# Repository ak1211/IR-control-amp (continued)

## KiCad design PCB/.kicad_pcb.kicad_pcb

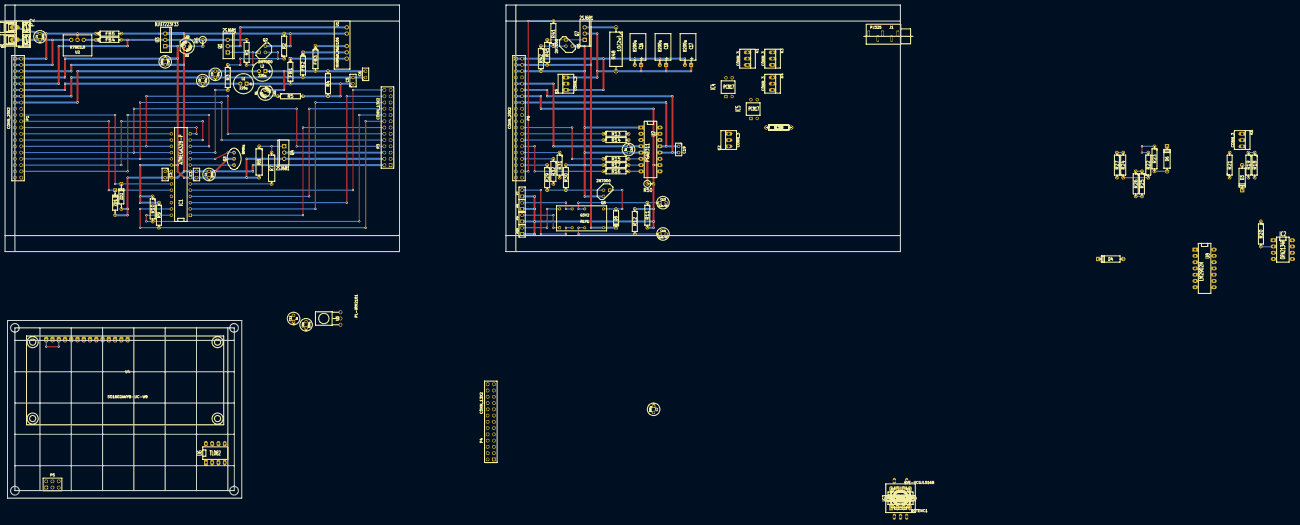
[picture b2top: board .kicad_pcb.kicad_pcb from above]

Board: 2 copper layers, 363.2 x 200.0 mm, 125 parts (0 on the bottom side), 102 nets.

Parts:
C1, C7, C10, C11: 100u; C1V5
C2, C3, C5, C6, C19: 0.1u; C1
C4: 220u; C1V5
C8, C9: 47u; C1V5
C12, C15: 1u; C1V5
C13, C14: 2.2u BP; C1V5
C16, C17, C18: 8200u; C1V7H
D1, D2: LED; LED-5MM
D3, D4, D6, D7: DIODE; D4
D5: DIODE; D3
FB1, FB2, FB3, FB4, FB5: FILTER; CP4
IC1: ATMEGA328-P; DIP-28__300
IC2, IC3: OPA2134P; DIP-8__300_ELL
IC4, IC5: PC817; DIP-4__300
J1: PJ325
K1, K2, K3, K4, K5, K6: CONN_3; PINHEAD1-3
L1, L2: 220u; C1V8
P1, P6: CONN_20X2; PIN_ARRAY_20X2
P2: CONN_2; AK300-2
P3, P4: CONN_13X2; pin_array_13x2
P5: CONN_6; pin_array_3x2
P7, P8, P9, P10: CONN_2; PIN_ARRAY_2X1
Q1, Q4, Q7: 2SJ681; TO220_VERTGDS
Q2, Q5, Q6: 2N7000; TO92DGS
Q3: 8MHz; CERALOCK
R1, R2, R30, R38, R39, R42: 10k; R4
R3, R29, R41: 10; R4
R4, R13, R14, R15, R16: 1k; R4
R5, R9, R10, R23, R24, R27, R28: 4.7k; R4
R6: 4.7k; R1
R7: 10; R5
R8: 10k; R5
R11, R12, R17: 47k; R4
R18, R19, R20, R21, R22, R25, R26, R33, R40, R43, R44, R46, R47, R49: 100k; R4
R31, R32: 220; R4
R34, R35, R36, R37: 47; R4
R45: 33k; R4
R48: 10(2w); R7
R50: 0; R1
RLY1: G5V2; G5V-2
ROTENC1: EVE-VCGJL016B; EVEV
SW1: RESET_SW; SW_PUSH_SMALL
U1: MINMAX_MAU106; MAU106
U2: R78E5.0; RECOM_R78E
U3: NJU7223F33; TO220_VERT123
U4: SO1602AWYB-UC-WB; SO1602
U5: PL-IRM2161
U6: TL082; DIP-8__300_ELL
U7: PGA2311; DIP-16__300_ELL
U8: LM2902N; DIP-14__300_ELL
ZD1, ZD2: 3.3V; DO-41

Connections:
+3.3V: C1.1, C3.1, C10.1, C12.1, IC1.7, IC1.20, P1.7, P1.8, P3.4, P4.4, P5.2, P6.7, P6.8, Q4.S, R8.2, R9.1, R10.1, U3.1, U5.3
+5.0V: C8.1, C19.2, IC2.8, IC3.8, L1.2, P1.11, P1.12, P6.11, P6.12, U6.8, U7.12, U8.4
+5V: C7.1, C15.1, FB4.2, P1.9, P1.10, P6.9, P6.10, Q1.S, R1.2, R6.1, U3.2, U7.4
+12V: C4.1, D5.2, P1.3, P1.4, P2.2, P6.3, P6.4, Q7.S, R45.2, R48.1, RLY1.1, U2.1
-5.0V: C9.2, C19.1, IC2.4, IC3.4, L2.2, P1.15, P1.16, P6.15, P6.16, U6.4, U7.13, U8.11
/analog_board/1ch.L: P7.2, RLY1.6
/analog_board/1ch.R: P8.2, RLY1.11
/analog_board/2ch.L: P9.2, RLY1.8
/analog_board/2ch.R: P10.2, RLY1.9
/analog_board/EVOL_SCLK: P6.24, R15.1
/analog_board/EVOL_SDI: P6.28, R14.1
/analog_board/EVOL_~CS: P6.26, R13.1
/analog_board/INPUT_CH.L: P6.20, R33.2, U8.7
/analog_board/INPUT_CH.R: P6.22, R49.2, U8.14
/analog_board/INRASH_CURRENT_LIMITTER_GATE: P6.38, R41.2
/analog_board/LINE_OUT.L: J1.4, K4.3
/analog_board/LINE_OUT.R: J1.2, K3.3
/analog_board/MISO/MAIN_AMP_STANDBY: P6.32, R31.1
/analog_board/MOSI/EVOL_MUTE: P6.30, R16.1
/analog_board/SCK/MAIN_AMP_MUTE: P6.34, R32.1
/analog_board/SELECT_SOURCE_GATE: P6.36, R29.1
/mpu_board/ANALOG_PWR_GATE: IC1.11, R3.2
/mpu_board/EVOL_SCLK: IC1.14, P1.24
/mpu_board/EVOL_SDI: IC1.16, P1.28
/mpu_board/EVOL_~CS: IC1.15, P1.26
/mpu_board/I2C_SCL: IC1.28, P3.18, P4.18, R10.2, U4.7
/mpu_board/I2C_SDA: IC1.27, P3.16, P4.16, R9.2, U4.8, U4.9
/mpu_board/INPUT_CH.L: IC1.23, P1.20, ZD2.2
/mpu_board/INPUT_CH.R: IC1.24, P1.22, ZD1.2
/mpu_board/INPUT_SW: IC1.4, P3.20, P4.20, ROTENC1.S
/mpu_board/INRASH_CURRENT_LIMITTER_GATE: IC1.12, P1.38
/mpu_board/IR_RECEIVER: IC1.5, P3.26, P4.26, U5.1
/mpu_board/MISO/MAIN_AMP_STANDBY: IC1.18, P1.32, P3.8, P4.8, P5.1
/mpu_board/MOSI/EVOL_MUTE: IC1.17, P1.30, P3.12, P4.12, P5.4
/mpu_board/ROTARYENC_A: IC1.2, P3.22, P4.22, ROTENC1.A
/mpu_board/ROTARYENC_B: IC1.3, P3.24, P4.24, ROTENC1.B
/mpu_board/SCK/MAIN_AMP_MUTE: IC1.19, P1.34, P3.10, P4.10, P5.3
/mpu_board/SELECT_SOURCE_GATE: IC1.13, P1.36
/mpu_board/~DISPLAY_PWR_GATE: IC1.6, R7.2
/mpu_board/~RESET: IC1.1, P3.14, P4.14, P5.5, SW1.1
AGND: C5.2, C6.1, C8.2, C9.1, FB2.2, J1.1, K3.1, K4.1, P1.13, P1.14, P6.13, P6.14, P7.1, P8.1, P9.1, P10.1, R11.2, R12.1, R21.2, R22.2, R23.1, R24.1, R50.2, U7.10, U7.15, U8.3, U8.5, U8.10, U8.12
DGND: C1.2, C2.2, C3.2, C7.2, C10.2, C11.2, C12.2, C15.2, D2.2, FB5.2, IC1.8, IC1.22, IC4.2, IC5.2, P1.5, P1.6, P3.2, P4.2, P5.6, P6.5, P6.6, Q2.S, Q3.2, Q5.S, Q6.S, R2.2, R17.2, R30.2, R42.2, R50.1, ROTENC1.COM, SW1.2, U1.2, U3.3, U4.1, U4.3, U4.4, U5.2, U7.1, U7.5, ZD1.1, ZD2.1
GNDPWR: C4.2, C16.2, C17.2, C18.2, FB5.1, K5.1, P1.1, P1.2, P2.1, P6.1, P6.2, U2.2
LINE_IN_L: C14.2, U6.3, U7.16
LINE_IN_R: C13.2, U6.5, U7.9
unnamed: D1.1, R5.1
unnamed: P3.6, Q4.D
unnamed: FB4.1, U2.3
unnamed: Q4.G, R7.1, R8.1
unnamed: FB1.1, U1.6
unnamed: FB2.1, U1.5
unnamed: FB3.1, U1.4
unnamed: Q1.G, Q2.D, R1.1
unnamed: D2.1, R6.2
unnamed: C2.1, IC1.21
unnamed: C11.1, P4.6, U4.2
unnamed: Q1.D, U1.1
unnamed: IC1.10, Q3.3
unnamed: IC1.9, Q3.1
unnamed: C5.1, FB1.2, L1.1, R4.1, R5.2
unnamed: C6.2, D1.2, FB3.2, L2.1, R4.2
unnamed: Q2.G, R2.1, R3.1
unnamed: D6.2, R40.2, R43.1, U8.9
unnamed: R20.2, R25.2, R26.2, R33.1, U8.6
unnamed: IC4.1, R31.2
unnamed: D3.1, D4.2, U8.1
unnamed: R18.1, R20.1, U6.1, U6.2
unnamed: D3.2, R18.2, R19.1, U8.2
unnamed: D6.1, D7.2, U8.8
unnamed: R44.2, R46.2, R47.2, R49.1, U8.13
unnamed: C13.1, R11.1, RLY1.13
unnamed: C14.1, R12.2, RLY1.4
unnamed: R16.2, U7.8
unnamed: R15.2, U7.6
unnamed: R14.2, U7.3
unnamed: R13.2, U7.2
unnamed: Q6.D, Q7.G, R45.1
unnamed: R40.1, R44.1, U6.6, U6.7
unnamed: D5.1, Q5.D, RLY1.16
unnamed: R17.1, U7.7
unnamed: IC5.4, K2.1
unnamed: IC4.4, K1.1
unnamed: K1.3, R38.2
unnamed: K2.3, R39.2
unnamed: IC4.3, K1.2, R38.1
unnamed: IC5.3, K2.2, R39.1
unnamed: IC5.1, R32.2
unnamed: Q5.G, R29.2, R30.1
unnamed: D7.1, R43.2, R46.1, R47.1
unnamed: D4.1, R19.2, R25.1, R26.1
unnamed: IC2.7, IC3.5, R35.1
unnamed: IC2.5, R22.1, U7.14
unnamed: IC3.1, IC3.2, R36.1
unnamed: IC3.6, IC3.7, R37.1
unnamed: C16.1, C17.1, C18.1, K5.3, Q7.D, R48.2
unnamed: IC2.3, R21.1, U7.11
unnamed: J1.5, R28.2, R35.2, R37.2
unnamed: IC2.6, R24.2, R28.1
unnamed: IC2.1, IC3.3, R34.1
unnamed: J1.3, R27.2, R34.2, R36.2
unnamed: IC2.2, R23.2, R27.1
unnamed: Q6.G, R41.1, R42.1

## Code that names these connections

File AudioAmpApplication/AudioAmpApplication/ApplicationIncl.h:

/*
 * This software for IR control headphone amplifier main board Rev:A2.0 or above.
 * https://github.com/ak1211/IR-control-amp
 *
 * Copyright (c) 2015 Akihiro Yamamoto http://ak1211.com
 *
 * This software is released under the MIT License.
 * https://github.com/ak1211/IR-control-amp/blob/master/LICENSE
 */

/*
 * ApplicationIncl.h
 * プロジェクト定義ヘッダファイル
 *
 * Created: 2015/01/04 19:57:16
 *  Author: akihiro
 */

#include <stdint-gcc.h>

#ifndef APPLICATIONINCL_H_
#define APPLICATIONINCL_H_

/*
 * PB0          -- pin 14 -- out    -- ~INRUSH_CURRENT_LIMITTER
 * PB1          -- pin 15 -- out    -- ANALOG_PWR_GATE
 * PB2          -- pin 16 -- out    -- SELECT_SOURCE
 * PB3(MOSI)    -- pin 17 -- out    -- AVRISP mkII and EVOL_SDI EVOL_MUTE
 * PB4(MISO)    -- pin 18 -- out    -- AVRISP mkII and EVOL_SCLK
 * PB5(SCK)     -- pin 19 -- out    -- AVRISP mkII and ~EVOL_CS
 * PB6(XTAL1)   -- pin  9 -- out    --
 * PB7(XTAL2)   -- pin 10 -- out    --
 *
 * 0b1111 1111 == 0xff
 *
 *
 * PC0(ADC0)    -- pin 23 -- in     -- L ch LEVEL INPUT
 * PC1(ADC1)    -- pin 24 -- in     -- R ch LEVEL INPUT
 * PC2          -- pin 25 -- out    -- ~MAIN_AMP_STANDBY
 * PC3          -- pin 26 -- out    -- ~MAIN_AMP_MUTE
 * PC4(SDA)     -- pin 27 -- out    -- I2C_SDA
 * PC5(SCL)     -- pin 28 -- out    -- I2C_SCL
 * PC6(~RESET)  -- pin  1 -- out    -- ~RESET
 *
 * 0b1111 1100 == 0xfc
 *
 *
 * PD0          -- pin  2 -- in     -- Rotary Encoder B
 * PD1          -- pin  3 -- in     -- Rotary Encoder A
 * PD2(INT0)    -- pin  4 -- in     -- ~INPUT SWITCH
 * PD3(INT1)    -- pin  5 -- in     -- ~IR_RECEIVER
 * PD4          -- pin  6 -- out    -- ~DISPLAY_PWR
 * PD5          -- pin 11 -- out    -- LED_B
 * PD6          -- pin 12 -- out    -- LED_G
 * PD7          -- pin 13 -- out    -- LED_R
 *
 * 0b1111 0000 == 0xf0
 *
 */

inline void initialize_iopin() {
    //ポートＢ初期化
    //すべて出力
    DDRB  = 0xff;
    //すべて出力なので、内蔵プルアップ無効
    PORTB = 0x00;

    //ポートＣ初期化
    //(PC0:ADC0), (PC1:ADC1)を入力に
    DDRC  = 0xfc;
    //ADCなので内蔵プルアップ無効
    PORTC = 0x00;

    //ポートＤ初期化
    DDRD  = 0xf0;
    //(PD2:~INPUT_SWITCH),
    //(PD1:Rotary Encoder A),
    //(PD0:Rotary Encoder B)
    //内蔵プルアップを有効
    PORTD = 0x07;
}

//
// OLED power pin
//

inline bool IOread_from_oled_power_on() {
    return bit_is_clear(PORTD, PD4);    //負論理
}
inline void IOwrite_to_oled_power_on() {
    PORTD &= ~_BV(PD4); //負論理
}
inline void IOwrite_to_oled_power_off() {
    PORTD |= _BV(PD4);  //負論理
}

//
// electric volume SDI pin
//
inline void IOwrite_to_LM1972_DATA_H() {
    PORTB |= _BV(PB3);
}
inline void IOwrite_to_LM1972_DATA_L() {
    PORTB &= ~_BV(PB3);
}
inline void IOwrite_to_LM1972_DATA_pwrsave() {
    IOwrite_to_LM1972_DATA_L();         // DATAをLに、省電力のため
}

//
// electric volume clock pin
//
inline void IOwrite_to_LM1972_CLOCK_H() {
    PORTB |= _BV(PB4);
}
inline void IOwrite_to_LM1972_CLOCK_L() {
    PORTB &= ~_BV(PB4);
}
inline void IOwrite_to_LM1972_CLOCK_pwrsave() {
    IOwrite_to_LM1972_CLOCK_L();            // CLOCKをLに、省電力のため
}

//
// electric volume ~EVOL_CS pin
//
inline void IOwrite_to_LM1972_LOADSHIFT_H() {
    PORTB |= _BV(PB5);
}
inline void IOwrite_to_LM1972_LOADSHIFT_L() {
    PORTB &= ~_BV(PB5);
}
inline void IOwrite_to_LM1972_LOADSHIFT_pwrsave() {
    IOwrite_to_LM1972_LOADSHIFT_L();        // LOADSHIFTをLに、省電力のため
}


//
// main amp standby pin
//
inline void IOwrite_to_main_amp_stanby_mode_enable() {
    PORTC &= ~_BV(PC2); //負論理
}
inline void IOwrite_to_main_amp_stanby_mode_disable() {
    PORTC |= _BV(PC2);  //負論理
}
inline void IOwrite_to_main_amp_stanby_mode_pwrsave() {
    PORTC &= ~_BV(PC2); //フォトカプラをoffに、省電力のため
}
//
// main amp mute pin
//
inline void IOwrite_to_main_amp_mute_mode_enable() {
    PORTC &= ~_BV(PC3); //負論理
}
inline void IOwrite_to_main_amp_mute_mode_disable() {
    PORTC |= _BV(PC3);  //負論理
}
inline void IOwrite_to_main_amp_mute_mode_pwrsave() {
    PORTC &= ~_BV(PC3); //フォトカプラをoffに、省電力のため
}

//
// rotary encoder
//
inline bool IOread_from_renc_A() {
    return bit_is_set(PIND, PD1);
}
inline bool IOread_from_renc_B() {
    return bit_is_set(PIND, PD0);
}

//
// input switch pin
//
inline bool IOread_from_input_switch() {
    return bit_is_clear(PIND, PD2); //負論理
}

//
// infra red receiver pin
//
inline bool IOread_from_IR_receiver() {
    return bit_is_clear(PIND, PD3); //負論理
}

//
// select source pin
//
inline void IOwrite_to_select_source_1() {
    PORTB &= ~_BV(PB2);
}
inline void IOwrite_to_select_source_2() {
    PORTB |= _BV(PB2);
}
inline uint8_t IOread_from_select_source() {
    return (bit_is_clear(PORTB, PB2)) ? 1 : 2;
}

//
// analog section power pin
//
inline void IOwrite_to_analog_section_power_on() {
    PORTB |= _BV(PB1);
}
inline void IOwrite_to_analog_section_power_off() {
    PORTB &= ~_BV(PB1);
}

//
// inrush current limitter pin
//
inline void IOwrite_to_inrush_current_limitter_enable() {
    PORTB &= ~_BV(PB0); //負論理
}
inline void IOwrite_to_inrush_current_limitter_disable() {
    PORTB |= _BV(PB0);  //負論理
}

//
// blue LED pin
//
inline void IOwrite_to_blue_LED_on() {
    PORTD |= _BV(PD5);
}
inline void IOwrite_to_blue_LED_off() {
    PORTD &= ~_BV(PD5);
}
inline bool IOread_from_blue_LED() {
    return bit_is_set(PIND, PD5);
}

//
// green LED pin
//
inline void IOwrite_to_green_LED_on() {
    PORTD |= _BV(PD6);
}
inline void IOwrite_to_green_LED_off() {
    PORTD &= ~_BV(PD6);
}
inline bool IOread_from_green_LED() {
    return bit_is_set(PIND, PD6);
}

//
// red LED pin
//
inline void IOwrite_to_red_LED_on() {
    PORTD |= _BV(PD7);
}
inline void IOwrite_to_red_LED_off() {
    PORTD &= ~_BV(PD7);
}
inline bool IOread_from_red_LED() {
    return bit_is_set(PIND, PD7);
}

//
// R/G/B LED pins control
//
inline void IOwrite_to_red_green_blue_LED(uint8_t rgb) {
    if (rgb & 0x4) {
        IOwrite_to_red_LED_on();
    } else {
        IOwrite_to_red_LED_off();
    }
    if (rgb & 0x2) {
        IOwrite_to_green_LED_on();
    } else {
        IOwrite_to_green_LED_off();
    }
    if (rgb & 0x1) {
        IOwrite_to_blue_LED_on();
    } else {
        IOwrite_to_blue_LED_off();
    }
}
inline uint8_t IOread_from_red_green_blue_LED() {
    return
        IOread_from_red_LED() << 2 |
        IOread_from_green_LED() << 1 |
        IOread_from_blue_LED();
}


#endif /* APPLICATIONINCL_H_ */

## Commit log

2016-02-19 first edit
2016-02-19 first added
2016-02-19 Update LICENSE
2016-02-19 file add
2016-02-20 fix a typo
2016-02-20 file added
2016-02-23 add .gitattributes
2016-02-25 2乗計算をループの外にした
2016-09-13 add KiCad project files
2016-09-13 first add KiCad project file
2016-10-19 fix the MIT license notation
2016-10-19 binary added
2016-10-19 V1.0
